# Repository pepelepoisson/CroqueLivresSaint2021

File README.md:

***

***
This repo contains files about a project called GeaiRareLit. It is all about building a small ESP8266 brain for a little bookcase installed outside of my local school. The device is solar powered and drives WS2812B leds + epaper when door is opened. ePaper is used to display an inspiring sentence from a famous author. Users passing by the bookself get the chance to read the sentence even tough they have no book to give or take. All project details are available on the [project page](http://www.chezpapietmamie.com/pcube/uncategorized/geairarelit/)
***

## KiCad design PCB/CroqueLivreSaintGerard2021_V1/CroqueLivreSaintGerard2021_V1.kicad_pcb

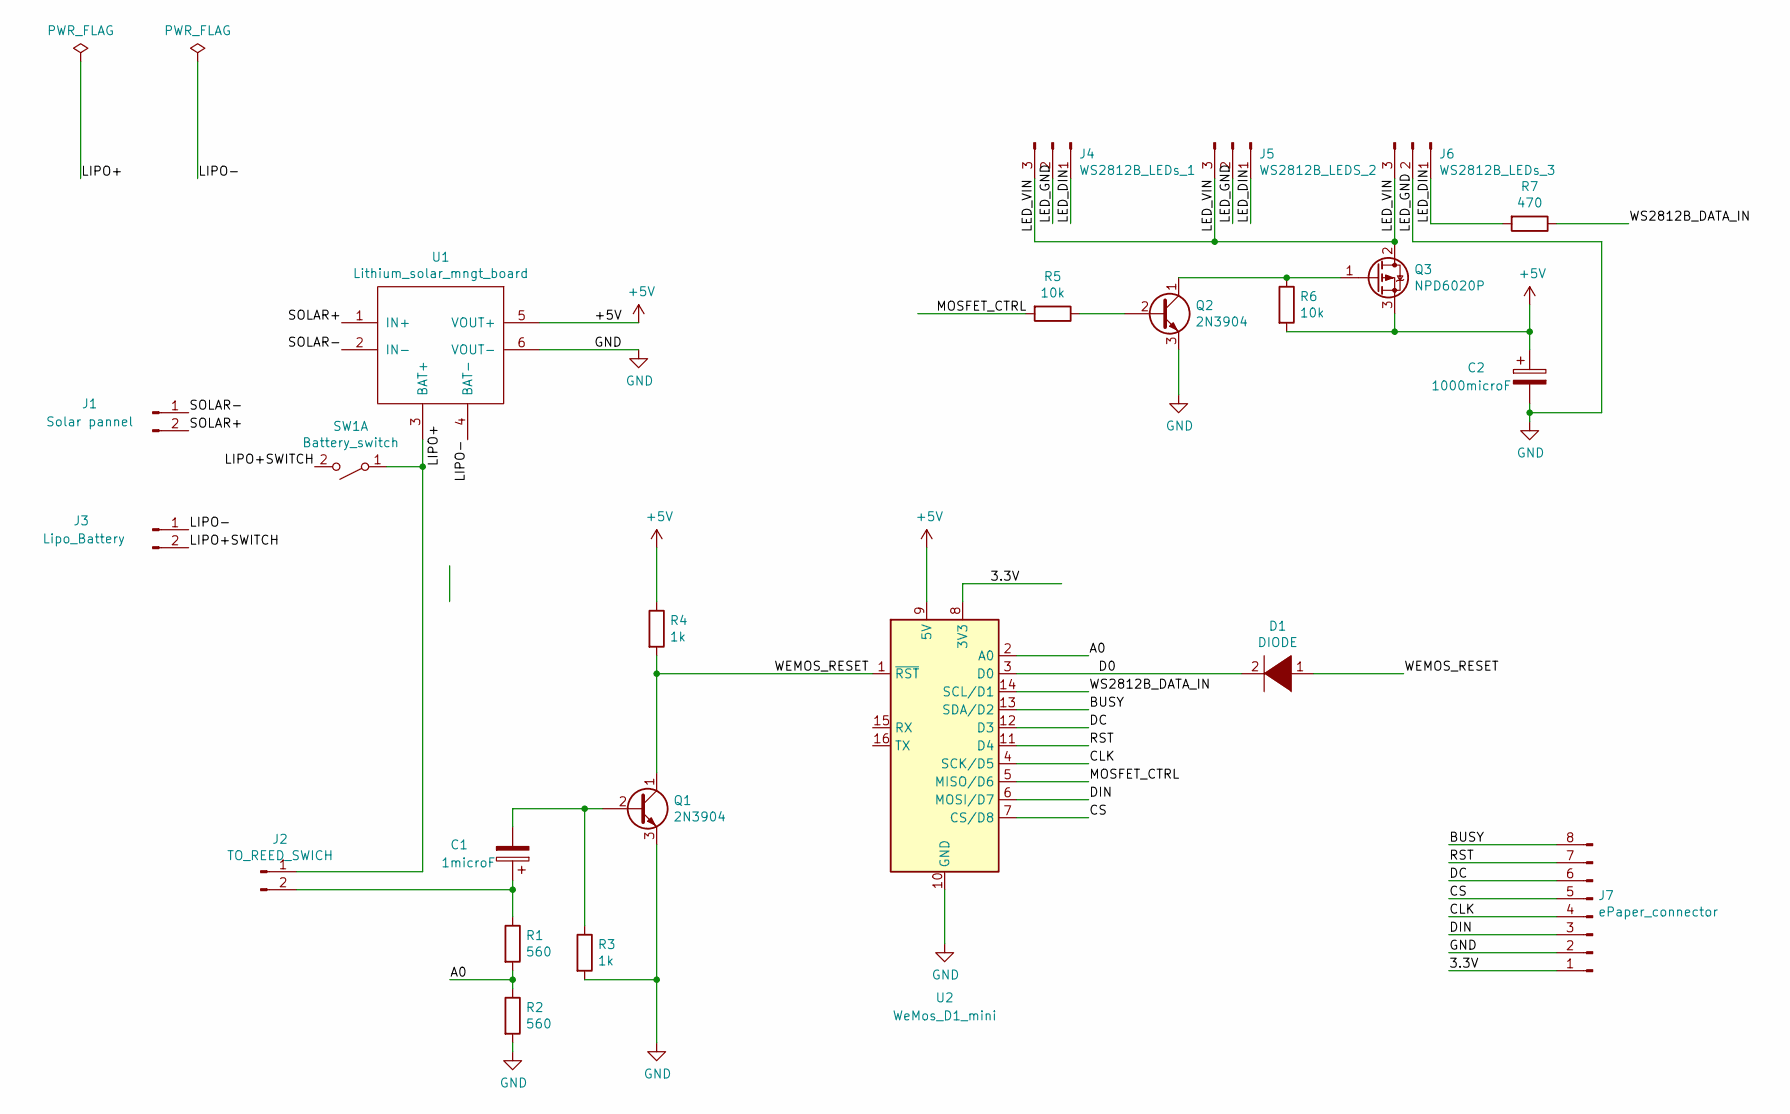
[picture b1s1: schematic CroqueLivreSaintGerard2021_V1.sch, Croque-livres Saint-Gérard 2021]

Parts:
C1: 1microF; CP_Radial_D6.3mm_P2.50mm
C2: 1000microF; Edge_CP_Radial_D12.5mm_P5.00mm
D1: DIODE; D_DO-41_SOD81_P10.16mm_Horizontal
J1: Solar pannel; JST_EH_S2B-EH_1x02_P2.50mm_Horizontal
J2: TO_REED_SWICH; PinHeader_1x02_P2.54mm_Horizontal
J3: Lipo_Battery; JST_EH_S2B-EH_1x02_P2.50mm_Horizontal
J4: WS2812B_LEDs_1; PinHeader_1x03_P2.54mm_Vertical
J5: WS2812B_LEDS_2; PinHeader_1x03_P2.54mm_Vertical
J6: WS2812B_LEDs_3; PinHeader_1x03_P2.54mm_Vertical
J7: ePaper_connector; PinSocket_1x08_P2.54mm_Horizontal
Q1, Q2: 2N3904; TO-92L_Inline_Wide
Q3: NPD6020P; TO-220-3_Horizontal_TabDown
R1, R2: 560; R_Axial_DIN0207_L6.3mm_D2.5mm_P10.16mm_Horizontal
R3, R4: 1k; R_Axial_DIN0207_L6.3mm_D2.5mm_P10.16mm_Horizontal
R5, R6: 10k; R_Axial_DIN0207_L6.3mm_D2.5mm_P10.16mm_Horizontal
R7: 470; R_Axial_DIN0207_L6.3mm_D2.5mm_P10.16mm_Horizontal
SW1: Battery_switch; SW_Slide_1P2T_CK_OS102011MS2Q
U1: Lithium_solar_mngt_board
U2: WeMos_D1_mini; WEMOS_D1_mini_light

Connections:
+5V: C2.1, Q3.3 (S), R4.1, R6.2, U1.5 (VOUT+), U2.9 (5V)
/3.3V: J7.1, U2.8 (3V3)
/A0: R1.2, R2.1, U2.2 (A0)
/BUSY: J7.8, U2.13 (SDA/D2)
/CLK: J7.4, U2.4 (SCK/D5)
/CS: J7.5, U2.7 (CS/D8)
/D0: D1.2 (A), U2.3 (D0)
/DC: J7.6, U2.12 (D3)
/DIN: J7.3, U2.6 (MOSI/D7)
/LED_DIN: J4.1, J5.1, J6.1, R7.2
/LED_VIN: J4.3, J5.3, J6.3, Q3.2 (D)
/LIPO+SWITCH: J3.2, SW1.2 (B); also elsewhere on the board
/LIPO-: J3.1, U1.4 (BAT-); also elsewhere on the board
/MOSFET_CTRL: R5.2, U2.5 (MISO/D6)
/RST: J7.7, U2.11 (D4)
/SOLAR+: J1.2, U1.1 (IN+); also elsewhere on the board
/SOLAR-: J1.1, U1.2 (IN-); also elsewhere on the board
/WEMOS_RESET: D1.1 (K), Q1.1 (C), R4.2, U2.1 (~RST)
/WS2812B_DATA_IN: R7.1, U2.14 (SCL/D1)
GND: C2.2, J4.2, J5.2, J6.2, J7.2, Q1.3 (E), Q2.3 (E), R2.2, R3.2, U1.6 (VOUT-), U2.10 (GND)
unnamed: C1.1, J2.2, R1.1
unnamed: C1.2, Q1.2 (B), R3.1
unnamed: J2.1, SW1.1 (A), U1.3 (BAT+)
unnamed: Q2.1 (C), Q3.1 (G), R6.1
unnamed: Q2.2 (B), R5.1

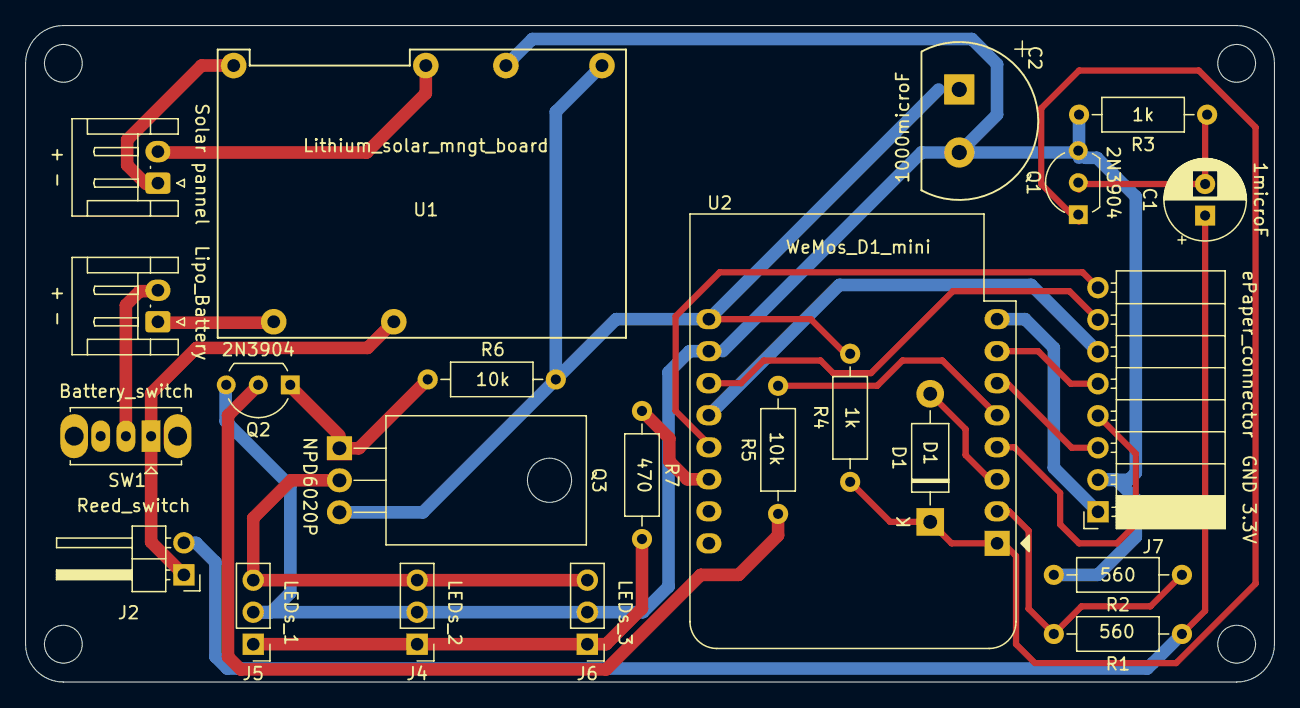
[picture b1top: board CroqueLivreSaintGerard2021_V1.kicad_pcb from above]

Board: 2 copper layers, 99.1 x 52.1 mm, 24 parts (1 on the bottom side), 25 nets.

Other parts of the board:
+ -: Lipo_Battery; JST_EH_S2B-EH_1x02_P2.50mm_Horizontal
+ -#2: Solar pannel; JST_EH_S2B-EH_1x02_P2.50mm_Horizontal
LOGO_papas_inventeurs_et_jeunes: LOGO_papas_inventeurs_et_jeunes (72x48mm)

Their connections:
/LIPO+SWITCH: + -.2; also elsewhere on the board
/LIPO-: + -.1; also elsewhere on the board
/SOLAR+: + -#2.2; also elsewhere on the board
/SOLAR-: + -#2.1; also elsewhere on the board

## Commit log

2021-03-10 First code with all main features working with V1 electronic circuit.
2021-05-12 Project as per the day of first release into real world!
2021-05-12 Changes to README
2021-05-14 Fixed a first bug - Automatically delete jog.json files if they are found corrupted based on their size - Not most robust solution but project works again ;-)
